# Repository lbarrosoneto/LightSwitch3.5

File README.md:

# LightSwitch3.5
This is a ESP32 Smart Light Switch with 3.5 Inch TFT Display, compatible with OpenHASP https://www.openhasp.com

The light switch is available in 2 configurations and  replaces standard mechanical switches for single / double gang.

## Vertical single-gang 

## Horizontal Double Gang

# Disclaimer
---
THIS PROJECT INVOLVES MONKEYING WITH HIGH VOLTAGE AND YOU COULD KILL YOURSELF 
AND/OR SET YOUR HOUSE ON FIRE

The end result is a thing that connects to live voltage and will be placed into 
your wall for years to come. It will not carry any sort of UL/CE/etc certification. 
Proceed with extreme caution.

EXCLUSION AND LIMITATION OF LIABILITY 
The developer shall, to
the maximum extent permitted by law, have no liability for
direct, indirect, special, incidental, consequential, exemplary,
punitive or other damages of any character including, without
limitation, procurement of substitute goods or services, loss of
use, data or profits, or business interruption, however caused
and on any theory of contract, warranty, tort (including
negligence), product liability or otherwise, arising in any way
in relation to the Covered Source, modified Covered Source
and/or the Making or Conveyance of a Product, even if advised of
the possibility of such damages, and You shall hold the
developer free and harmless from any liability, costs,
damages, fees and expenses, including claims by third parties,
in relation to such use.
      
---

# Hardware Design

2 PCBs compose the hardware design, that is available from https://github.com/lbarrosoneto/LightSwitch3.5/tree/main/HWDesign

## ESP32 Display Controller

## Relay and Power Board

# 3D Print Files
3D print design files for single and double gang versions is available from https://github.com/lbarrosoneto/LightSwitch3.5/tree/main/3DPrintCase

# Programming the LightSwitch3.5
Follow the instructions from https://www.openhasp.com/0.7.0/firmware/compiling/local/#native-windows-build

Lightswitch3.5 is compatible with the esp32-touchdown https://github.com/DustinWatts/esp32-touchdown

The Relays are connected to IO12 and IO13, so, those ports need to be configured "Pin Output" in the Light Switch Web Interface (Under Configuration->GPIO Settings): 

The hardware design is copyright (c) Luiz Oliveira Neto <lboneto@gmail.com> and licensed under [CERN Open Hardware Licence Version 2 - Strongly Reciprocal](https://github.com/lbarrosoneto/LightSwitch3.5)

The 3D Prints are copyright (c) Luiz Oliveira Neto <lboneto@gmail.com>  and licensed Creative Commons share alike.

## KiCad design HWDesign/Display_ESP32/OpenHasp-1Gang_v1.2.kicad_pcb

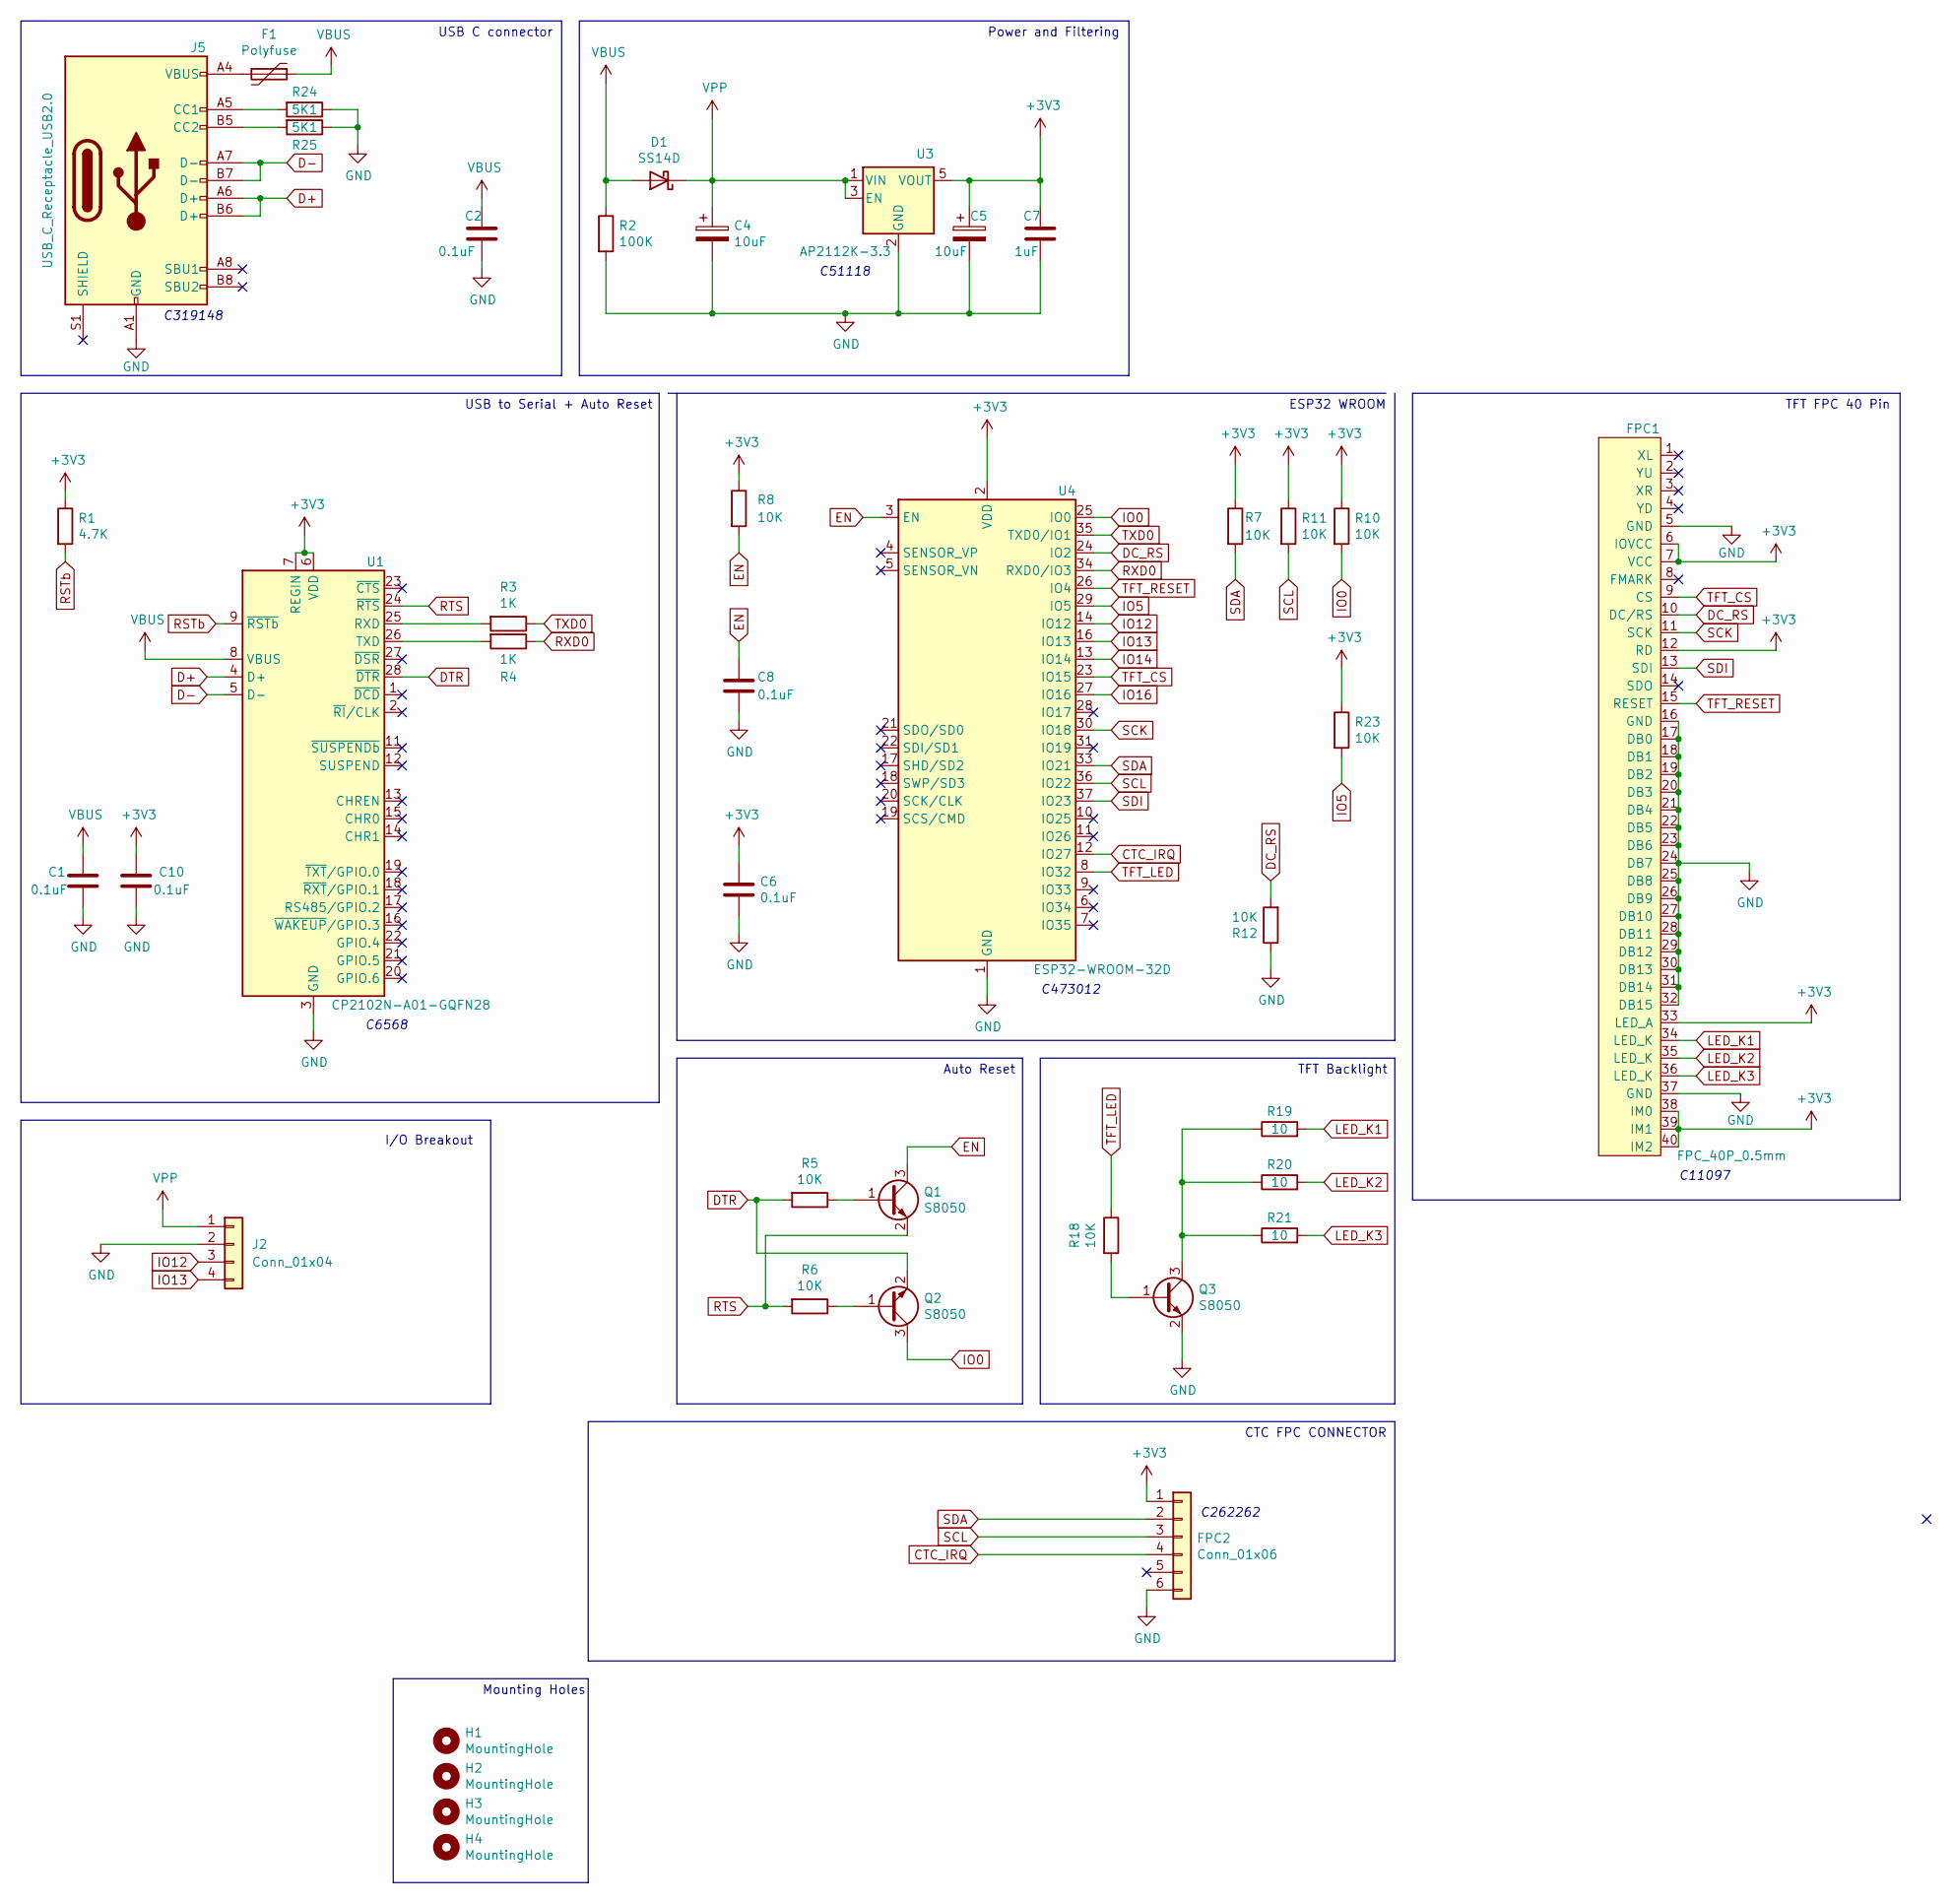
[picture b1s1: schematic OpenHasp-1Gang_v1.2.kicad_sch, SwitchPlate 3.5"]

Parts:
C1, C2, C6, C8, C10: 0.1uF; C_0603_1608Metric; LCSC C1591
C4, C5: 10uF; CP_EIA-3216-18_Kemet-A; LCSC C7177
C7: 1uF; C_0603_1608Metric; LCSC C1592
D1: SS14D; D_SMA; LCSC C83912
F1: Polyfuse; Fuse_0805_2012Metric; LCSC C151146
FPC1: FPC_40P_0.5mm; Hirose_FH12-40S-0.5SH_1x40-1MP_P0.50mm_Horizontal_flipped_c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; LCSC C11097
FPC2: Conn_01x06; Hirose_FH12-6S-0.5SH_1x06-1MP_P0.50mm_Horizontal; LCSC C262262
H1, H2, H3, H4: MountingHole; MountingHole_2.5mm_Pad_Via
J2: Conn_01x04; JST_PH_S4B-PH-SM4-TB_1x04-1MP_P2.00mm_Horizontal
J5: USB_C_Receptacle_USB2.0; USB_C_Receptacle_XKB_U262-16XN-4BVC11; LCSC C319148
Q1, Q2, Q3: S8050; SOT-23; LCSC C402279
R1: 4.7K; R_0603_1608Metric; LCSC C88615
R2: 100K; R_0603_1608Metric; LCSC C73806
R3, R4: 1K; R_0603_1608Metric; LCSC C73797
R5, R6, R7, R8, R10, R11, R12, R18, R23: 10K; R_0603_1608Metric; LCSC C99198
R19, R20, R21: 10; R_0603_1608Metric; LCSC C176153
R24, R25: 5K1; R_0603_1608Metric; LCSC C73801
U1: CP2102N-A01-GQFN28; QFN-28-1EP_5x5mm_P0.5mm_EP3.35x3.35mm; LCSC C6568
U3: AP2112K-3.3; SOT-23-5; LCSC C150742
U4: ESP32-WROOM-32D; ESP32-WROOM-32; LCSC C473012

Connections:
+3V3: C5.1, C6.1, C7.1, C10.1, FPC1.6 (IOVCC), FPC1.7 (VCC), FPC1.12 (RD), FPC1.33 (LED_A), FPC1.38 (IM0), FPC1.39 (IM1), FPC1.40 (IM2), FPC2.1, R1.1, R7.1, R8.1, R10.1, R11.1, R23.1, U1.6 (VDD), U1.7 (REGIN), U3.5 (VOUT), U4.2 (VDD)
CTC_IRQ: FPC2.4, U4.12 (IO27)
D+: J5.A6 (D+), J5.B6 (D+), U1.4 (D+)
D-: J5.A7 (D-), J5.B7 (D-), U1.5 (D-)
DC_RS: FPC1.10 (DC/RS), R12.2, U4.24 (IO2)
DTR: Q2.2 (B), R5.2, U1.28 (~DTR)
EN: C8.1, Q1.3 (C), R8.2, U4.3 (EN)
GND: C1.2, C2.2, C4.2, C5.2, C6.2, C7.2, C8.2, C10.2, FPC1.5 (GND), FPC1.16 (GND), FPC1.17 (DB0), FPC1.18 (DB1), FPC1.19 (DB2), FPC1.20 (DB3), FPC1.21 (DB4), FPC1.22 (DB5), FPC1.23 (DB6), FPC1.24 (DB7), FPC1.25 (DB8), FPC1.26 (DB9), FPC1.27 (DB10), FPC1.28 (DB11), FPC1.29 (DB12), FPC1.30 (DB13), FPC1.31 (DB14), FPC1.32 (DB15), FPC1.37 (GND), FPC2.6, J2.2, J5.A1 (GND), J5.A12 (GND), J5.B1 (GND), J5.B12 (GND), Q3.2 (B), R2.2, R12.1, R24.1, R25.1, U1.3 (GND), U1.29 (GND), U3.2 (GND), U4.1 (GND), U4.15 (GND), U4.38 (GND), U4.39 (GND)
IO0: Q2.3 (C), R10.2, U4.25 (IO0)
IO5: R23.2, U4.29 (IO5)
IO12: J2.3, U4.14 (IO12)
IO13: J2.4, U4.16 (IO13)
IO14: U4.13 (IO14)
IO16: U4.27 (IO16)
LED_K1: FPC1.34 (LED_K), R19.2
LED_K2: FPC1.35 (LED_K), R20.2
LED_K3: FPC1.36 (LED_K), R21.2
unnamed: F1.2, J5.A4 (VBUS), J5.A9 (VBUS), J5.B4 (VBUS), J5.B9 (VBUS)
unnamed: J5.A5 (CC1), R24.2
unnamed: J5.B5 (CC2), R25.2
unnamed: Q1.1 (E), R5.1
unnamed: Q2.1 (E), R6.1
unnamed: Q3.1 (E), R18.2
unnamed: Q3.3 (C), R19.1, R20.1, R21.1
unnamed: R3.2, U1.25 (RXD)
unnamed: R4.2, U1.26 (TXD)
RSTb: R1.2, U1.9 (~RSTb)
RTS: Q1.2 (B), R6.2, U1.24 (~RTS)
RXD0: R4.1, U4.34 (RXD0/IO3)
SCK: FPC1.11 (SCK), U4.30 (IO18)
SCL: FPC2.3, R11.2, U4.36 (IO22)
SDA: FPC2.2, R7.2, U4.33 (IO21)
SDI: FPC1.13 (SDI), U4.37 (IO23)
TFT_CS: FPC1.9 (CS), U4.23 (IO15)
TFT_LED: R18.1, U4.8 (IO32)
TFT_RESET: FPC1.15 (RESET), U4.26 (IO4)
TXD0: R3.1, U4.35 (TXD0/IO1)
VBUS: C1.1, C2.1, D1.2 (A), F1.1, R2.1, U1.8 (VBUS)
VPP: C4.1, D1.1 (K), J2.1, U3.1 (VIN), U3.3 (EN)

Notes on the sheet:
I/O Breakout
C262262
USB to Serial + Auto Reset
C11097
C473012
CTC FPC CONNECTOR
TFT Backlight
C51118
TFT FPC 40 Pin
Mounting Holes
USB C connector
Power and Filtering
Auto Reset
ESP32 WROOM
C6568
C319148

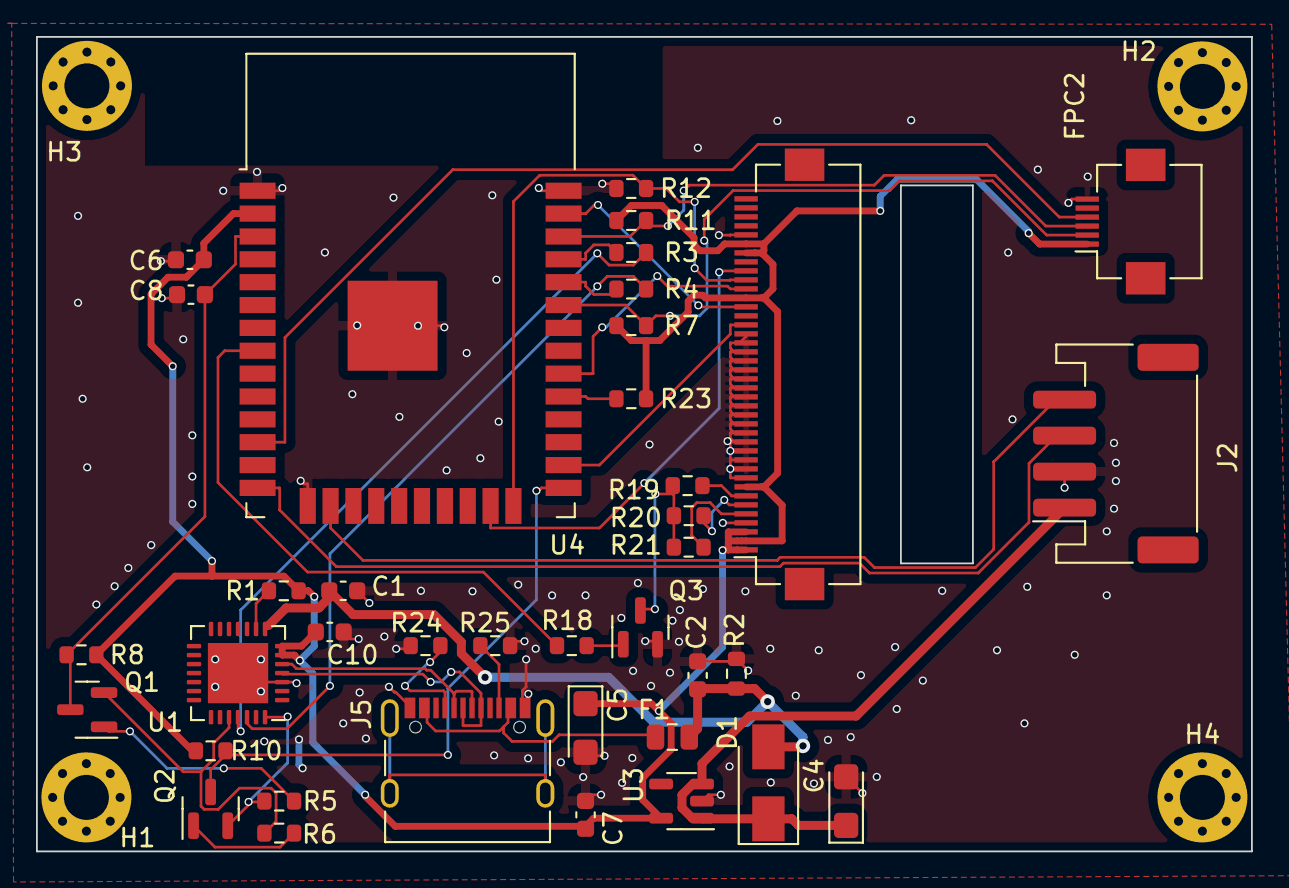
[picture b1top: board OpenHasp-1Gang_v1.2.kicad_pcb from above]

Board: 2 copper layers, 67.5 x 45.2 mm, 42 parts (0 on the bottom side), 37 nets.

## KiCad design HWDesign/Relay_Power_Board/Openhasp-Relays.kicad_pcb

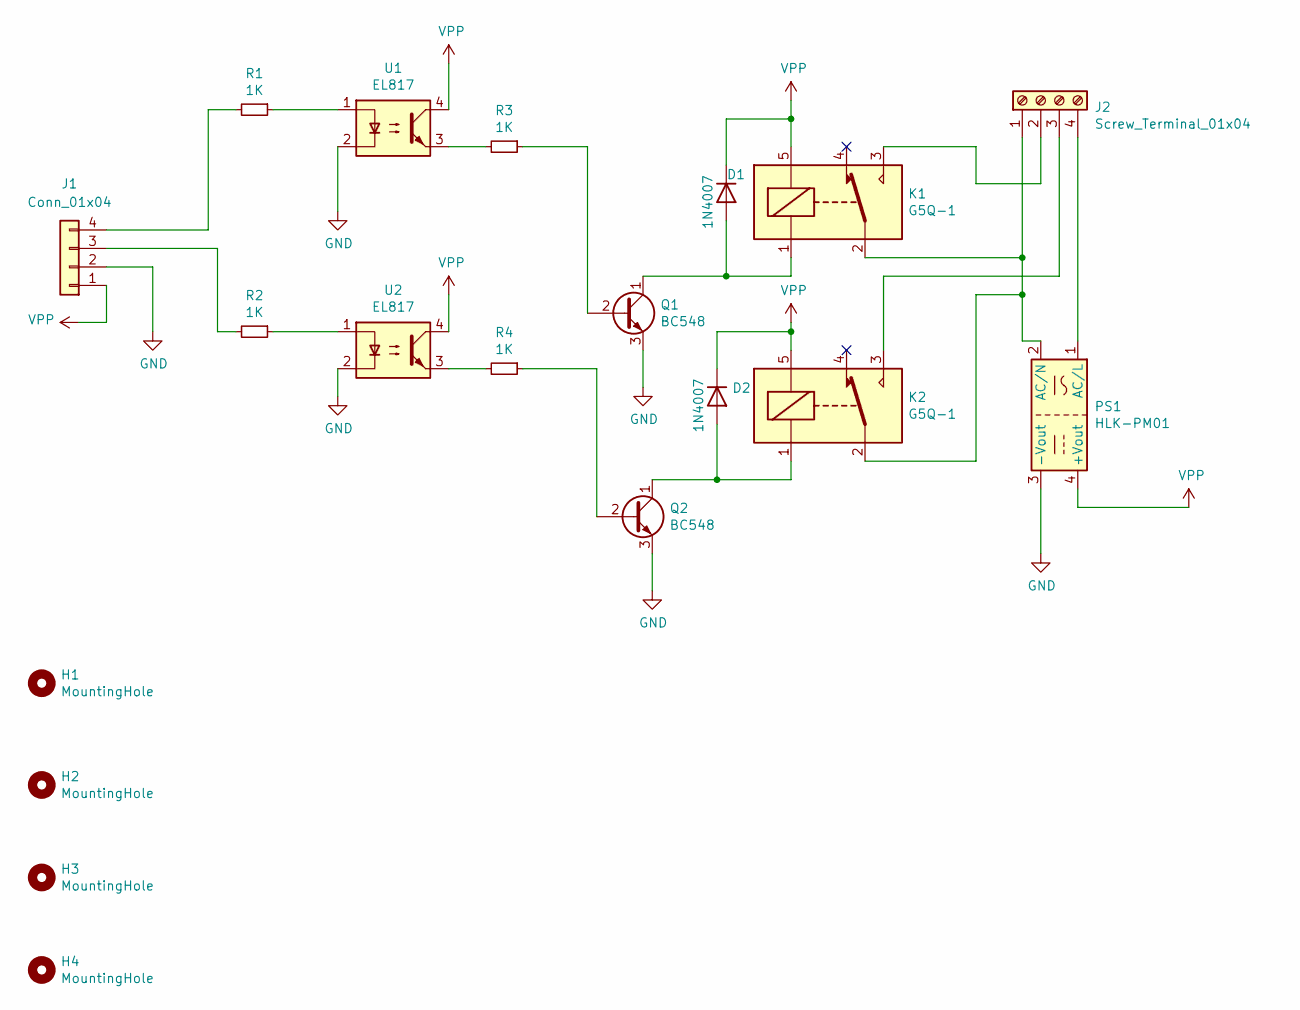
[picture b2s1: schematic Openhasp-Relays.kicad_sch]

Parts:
D1, D2: 1N4007; D_DO-41_SOD81_P10.16mm_Horizontal
H1, H2, H3, H4: MountingHole; MountingHole_2.2mm_M2_Pad_Via
J1: Conn_01x04; PinSocket_1x04_P2.54mm_Vertical
J2: Screw_Terminal_01x04; TE_MATE-N-LOK_350211-1_1x04_P5.08mm_Vertical
K1, K2: G5Q-1; Relay_SPDT_Omron-G5Q-1
PS1: HLK-PM01; Converter_ACDC_HiLink_HLK-PMxx
Q1, Q2: BC548; TO-92_Inline
R1, R2, R3, R4: 1K; R_Axial_DIN0204_L3.6mm_D1.6mm_P2.54mm_Vertical
U1, U2: EL817; DIP-4_W7.62mm

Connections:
GND: J1.2, PS1.3 (-Vout), Q1.3 (E), Q2.3 (E), U1.2, U2.2
unnamed: D1.2 (A), K1.1, Q1.1 (C)
unnamed: D2.2 (A), K2.1, Q2.1 (C)
unnamed: J1.3, R2.2
unnamed: J1.4, R1.2
unnamed: J2.1, K1.2, K2.2, PS1.2 (AC/N)
unnamed: J2.2, K1.3
unnamed: J2.3, K2.3
unnamed: J2.4, PS1.1 (AC/L)
unnamed: Q1.2 (B), R3.1
unnamed: Q2.2 (B), R4.1
unnamed: R1.1, U1.1
unnamed: R2.1, U2.1
unnamed: R3.2, U1.3
unnamed: R4.2, U2.3
VPP: D1.1 (K), D2.1 (K), J1.1, K1.5, K2.5, PS1.4 (+Vout), U1.4, U2.4

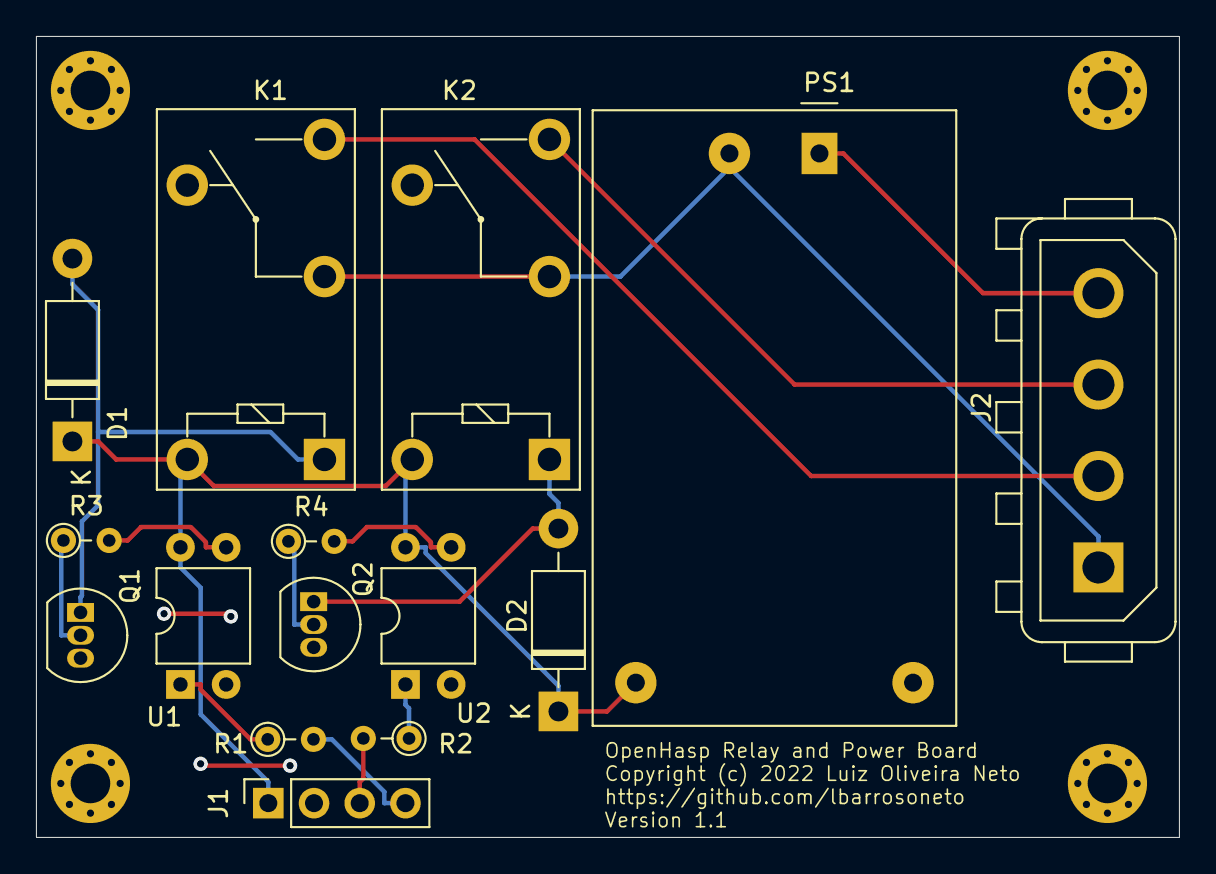
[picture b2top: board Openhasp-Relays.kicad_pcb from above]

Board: 2 copper layers, 63.5 x 44.5 mm, 19 parts (0 on the bottom side), 16 nets.

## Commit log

2024-02-16 Initial Versions
2024-02-16 Adding License, COPYING and Relay board design
2024-02-16 adding Copyright
2024-02-16 Adding correct CERN-OHL-S
    Adding correct CERN-OHL-S
2024-02-16 Update COPYING
2024-02-16 Deleting COPYING FILE
2024-02-16 Removing unecessary files
2024-02-16 Adding gerber/libraryfiles
2024-02-17 Adding more detailed Readme.md
    Readme.md is being updated to include:
    - Pictures
    - Hardware design details
    - 3D Print details
2024-02-17 Update README.md - Adding GPIO Setting Information
    Adding GPIO Setting information and screenshot
2024-02-17 Update README.md - Adding Disclaimer
    Adding disclaimer with exclusion and limitation of liability
2024-02-17 Update README.md - fixing disclaimer - adding license for 3dprints
2024-02-17 Add LICENSE to 3D PRINTS
2024-02-17 Update LICENSE
    Adding CCSA 2.0

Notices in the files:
HWDesign/Display_ESP32/OpenHasp-1Gang_v1.2.kicad_pcb:
Copyright (c) 2022 Luiz Oliveira Neto
